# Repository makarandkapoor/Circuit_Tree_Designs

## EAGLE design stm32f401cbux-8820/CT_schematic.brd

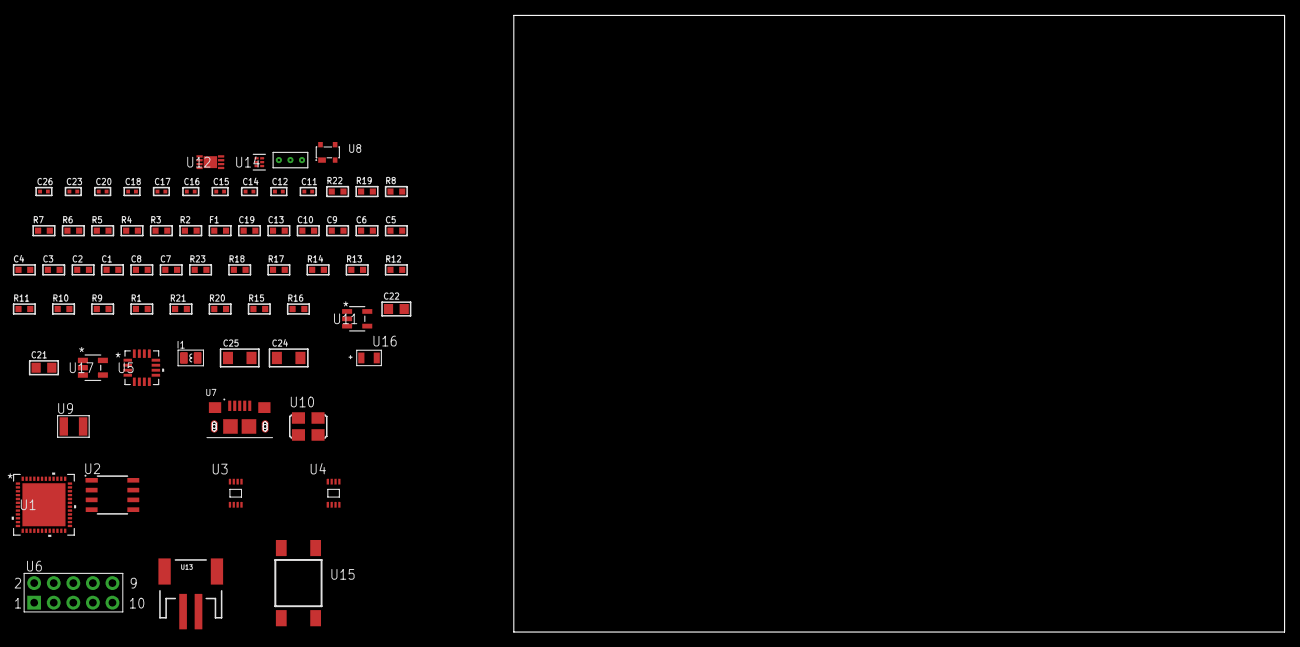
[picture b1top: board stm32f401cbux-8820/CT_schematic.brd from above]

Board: 2 copper layers, 69 parts (0 on the bottom side), 45 nets, no tracks yet.

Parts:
C1, C10, C13, C19: 1e-06; C0603
C2, C3, C4, C5, C6: 1e-07; C0603
C7: 4.7e-06; C0603
C8: 2.2e-06; C0603
C9: 1e-08; C0603
C11, C12: 1e-11; C0402
C14, C15, C16, C20, C26: 1e-08; C0402
C17, C18, C23: 1e-07; C0402
C21, C22: 1e-05; C0805
C24, C25: 1e-05; C1206
F1: 240.0; L0603
I1: 3.3e-06; L0806
R1, R9, R10, R11, R12, R13, R14, R17, R18, R23: 10000.0; R0603
R2: 1000.0; R0603
R3: 1600.5; R0603
R4: 4700.0; R0603
R5, R6, R7, R8: 2200.0; R0603
R15: 220000.0; R0603
R16: 1000000.0; R0603
R19: 9100.0; R0603
R20: 680000.0; R0603
R21: 120000.0; R0603
R22: 2000.0; R0603
U1: stm32f401CBU6; UFQFPN48
U2: AT25040B-SSHL-T; SOIC-8
U3: 24AA04-I/MC; TDFN-8/6MM
U4: 24AA08T-I/MNY; TDFN-8/6MM
U5: TSC2046IRGVR; VQFN-16
U6: HTSS-105-01-G-D
U7: 10118193-0001LF; FCI_10118193-0001LF
U8: prtr5v0u2ax; SOT143B
U9: ABS07-32.768KHZ-7-T
U10: ASFL1-25MHZ-NCS; ASFL1
U11: ltc3406es5; TSOT-23-5
U12: MCP73831T-2ACI/MC; DFN8_2X3MC
U13: S2B-PH-SM4-TB(LF)(SN); JST-2-SMD
U14: TPS3895ADRYR; SON-6
U15: 4-1437565-2; SW_4-1437565-2
U16: Q65110A2395; LGM67K-G1J2-24-Z
U17: nc7sz125m5x; NC7SZ125M5X
U18: Dummy; DUMMY_PACKAGE_149

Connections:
CLK_CRYSTAL_U1_3: C11.1, U1.3, U9.1
CLK_CRYSTAL_U1_4: C12.1, U1.4, U9.2
CLK_U1_5: U1.5, U10.3
GND: C1.2, C2.2, C3.2, C4.2, C5.2, C6.2, C7.2, C8.2, C9.2, C10.2, C11.2, C12.2, C13.2, C14.2, C15.2, C16.2, C17.2, C18.2, C19.2, C20.2, C21.2, C22.1, C22.2, C23.2, C24.2, C25.2, C26.2, R2.2, R9.2, R15.2, R19.2, R21.2, R22.2, U1.8, U1.23, U1.35, U1.47, U1.49, U2.4, U3.4, U4.4, U5.10, U6.9, U7.5, U7.6, U7.7, U7.8, U7.9, U8.1, U10.2, U11.2, U12.6, U12.9, U13.2, U14.2, U16.C, U17.1, U17.3, U18.1
INPUT_USBPOWER_5V: C13.1, C24.1, R23.2, U1.30, U7.1, U8.4, U12.1, U12.2
NET_U1_7: R4.1, U1.7, U17.4
NET_U1_9: C9.1, C10.1, F1.1, U1.9
NET_U1_21: R7.1, U1.21, U3.6
NET_U1_22: C8.1, U1.22
NET_U1_39: R8.1, U1.39, U3.5
NET_U1_42: R5.1, U1.42, U4.6
NET_U1_43: R6.1, U1.43, U4.5
NET_U1_44: R9.1, U1.44
NET_U1_45: R3.1, U1.45, U16.A
NET_U1_46: R1.1, U1.46, U15.3, U15.4
NET_U2_3: R10.1, U2.3
NET_U2_7: R12.1, U2.7
NET_U5_15: R14.1, U5.15
NET_U6_3: U5.7, U6.3
NET_U6_4: U5.9, U6.4
NET_U6_5: U5.6, U6.5
NET_U6_6: U5.8, U6.6
NET_U11_3: I1.1, U11.3
NET_U11_5: R15.1, R16.1, U11.5
NET_U11_ATNET_3: I1.2, R16.2
NET_U12_5: R23.1, U12.5
NET_U12_8: R22.1, U12.8
NET_U14_1: R18.1, R19.1, U14.1
NET_U14_3: R20.2, R21.1, U14.3
NET_U14_4: R17.1, U14.4, U17.2
NET_U15_1: R2.1, U15.1, U15.2
PROC_SPI1_MISO: U1.16, U5.16
PROC_SPI1_MOSI: U1.17, U5.2
PROC_SPI1_NSS: R13.1, U1.14, U5.3
PROC_SPI1_SCK: U1.15, U5.4
PROC_SPI2_MISO: U1.27, U2.2
PROC_SPI2_MOSI: U1.28, U2.5
PROC_SPI2_NSS: R11.1, U1.25, U2.1
PROC_SPI2_SCK: U1.26, U2.6
PROC_TIM1_CH2N: U1.18, U18.2
PROC_TIM1_CH3: U1.31, U18.3
PROC_USB_OTG_FS_DM: U1.32, U7.2, U8.3
PROC_USB_OTG_FS_DP: U1.33, U7.3, U8.2
VCC_S1_3V7: C21.1, C25.1, U11.4, U12.3, U12.4, U13.1
VCC_TIER1_3V3: C1.1, C2.1, C3.1, C4.1, C5.1, C6.1, C7.1, C14.1, C15.1, C16.1, C17.1, C18.1, C19.1, C20.1, C22.2, C23.1, C26.1, F1.2, I1.2, R1.2, R3.2, R4.2, R5.2, R6.2, R7.2, R8.2, R10.2, R11.2, R12.2, R13.2, R14.2, R16.2, R17.2, R18.2, R20.1, U1.1, U1.24, U1.36, U1.48, U2.8, U3.7, U3.8, U4.7, U4.8, U5.5, U5.14, U10.4, U14.6, U17.5

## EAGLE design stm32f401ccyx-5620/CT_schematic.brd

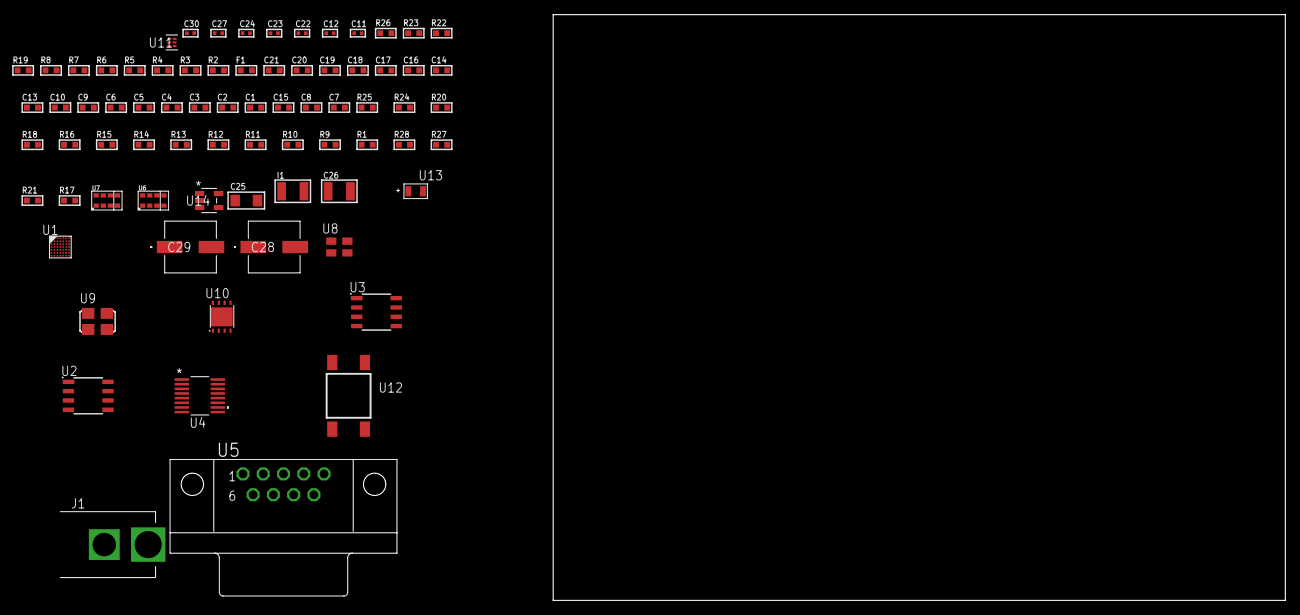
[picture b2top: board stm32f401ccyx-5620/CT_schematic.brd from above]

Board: 2 copper layers, 100.0 x 80.0 mm, 75 parts (0 on the bottom side), 51 nets, no tracks yet.

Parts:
C1, C10, C13, C14, C16, C17, C18, C19, C20, C21: 1e-06; C0603
C2, C3, C4, C5, C6: 1e-07; C0603
C7: 4.7e-06; C0603
C8: 2.2e-06; C0603
C9: 1e-08; C0603
C11, C12, C22, C23, C24, C30: 1e-08; C0402
C15: 2.2e-07; C0603
C25: 1e-05; C1206
C26: 1e-05; C1210
C27: 1e-07; C0402
C28, C29: 0.0001; EXV-9H
F1: 240.0; L0603
I1: 1e-05; L1210
J1: PJ-037B; PJ-037B_PACKAGE
R1, R9, R10, R11, R12, R13, R14, R15, R16, R18, R20, R24, R25: 10000.0; R0603
R2, R23: 1000.0; R0603
R3: 1600.5; R0603
R4: 4700.0; R0603
R5, R6, R7, R8: 2200.0; R0603
R17, R21: 100000.0; R0603
R19: 22.0; R0603
R22: 2231.0; R0603
R26: 9100.0; R0603
R27: 680000.0; R0603
R28: 120000.0; R0603
U1: STM32F401CCY6; WLCSP49
U2: AT25010B-SSHL-T; SOIC-8
U3: AT25640B-SSHL-T; SOIC-8
U4: LTC2804CGN-1#PBF; SSOP-16
U5: 182-009-113R531; 182-009-MALE
U6, U7: TMD27711; SMD-8
U8: ASEK-32.768KHz-ECST; ASEK
U9: ASFL1-25MHZ-NCS; ASFL1
U10: LP3878SDX-ADJ/NOPB; WSON-8
U11: TPS3895ADRYR; SON-6
U12: 4-1437565-2; SW_4-1437565-2
U13: Q65110A2395; LGM67K-G1J2-24-Z
U14: nc7sz125m5x; NC7SZ125M5X

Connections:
CLK_U1_C7: U1.C7, U8.3
CLK_U1_D7: U1.D7, U9.3
GND: C1.2, C2.2, C3.2, C4.2, C5.2, C6.2, C7.2, C8.2, C9.2, C10.2, C11.2, C12.2, C13.2, C14.2, C16.2, C17.2, C18.2, C19.2, C20.2, C21.2, C22.2, C23.2, C24.2, C25.2, C26.2, C27.2, C28.2, C29.2, C30.2, J1.2, R2.2, R9.2, R23.2, R26.2, R28.2, U1.A6, U1.B1, U1.D3, U1.E6, U2.4, U3.4, U4.8, U5.5, U6.3, U7.3, U8.2, U9.2, U10.3, U10.PAD, U11.2, U13.C, U14.1, U14.3
NET_U1_A3: R8.1, U1.A3, U7.8
NET_U1_A5: R9.1, U1.A5
NET_U1_B5: R5.1, U1.B5, U6.2
NET_U1_B6: R10.1, U1.B6
NET_U1_C5: R6.1, U1.C5, U6.8
NET_U1_E3: R7.1, U1.E3, U7.2
NET_U1_E7: R4.1, U1.E7, U14.4
NET_U1_F7: C9.1, C10.1, F1.1, U1.F7
NET_U1_G2: C8.1, U1.G2
NET_U1_G6: R3.1, U1.G6, U13.A
NET_U1_G7: R1.1, U1.G7, U12.3, U12.4
NET_U2_3: R11.1, U2.3
NET_U2_7: R13.1, U2.7
NET_U3_3: R14.1, U3.3
NET_U3_7: R16.1, U3.7
NET_U4_6: C13.1, U4.6
NET_U4_7: C15.1, I1.2, U4.7
NET_U4_9: C14.1, U4.9
NET_U4_10: C15.2, U4.10
NET_U4_11: R17.1, U4.11
NET_U5_2: U4.1, U5.2
NET_U5_3: U4.3, U5.3
NET_U5_7: U4.2, U5.7
NET_U5_8: U4.4, U5.8
NET_U6_4: C19.1, R19.1, U6.4
NET_U6_7: R18.1, U6.7
NET_U7_7: R20.1, U7.7
NET_U10_1: C24.1, U10.1
NET_U10_6: R22.2, R23.1, U10.6
NET_U10_8: R21.1, U10.8
NET_U11_1: R25.1, R26.1, U11.1
NET_U11_3: R27.2, R28.1, U11.3
NET_U11_4: R24.1, U11.4, U14.2
NET_U12_1: R2.1, U12.1, U12.2
PROC_SPI1_MISO: U1.A4, U2.2
PROC_SPI1_MOSI: U1.B4, U2.5
PROC_SPI1_NSS: R12.1, U1.A2, U2.1
PROC_SPI1_SCK: U1.F5, U2.6
PROC_SPI2_MISO: U1.F1, U3.2
PROC_SPI2_MOSI: U1.E1, U3.5
PROC_SPI2_NSS: R15.1, U1.E2, U3.1
PROC_SPI2_SCK: U1.G1, U3.6
PROC_USART1_CTS: U1.C1, U4.13
PROC_USART1_RTS: U1.C3, U4.15
PROC_USART1_RX: U1.C2, U4.16
PROC_USART1_TX: U1.C4, U4.14
VCC_S1_5V3: C25.1, C28.1, C29.1, J1.1, R21.2, U10.4
VCC_TIER1_3V3: C1.1, C2.1, C3.1, C4.1, C5.1, C6.1, C7.1, C11.1, C12.1, C16.1, C17.1, C18.1, C20.1, C21.1, C22.1, C23.1, C26.1, C27.1, C30.1, F1.2, I1.1, R1.2, R3.2, R4.2, R5.2, R6.2, R7.2, R8.2, R10.2, R11.2, R12.2, R13.2, R14.2, R15.2, R16.2, R17.2, R18.2, R19.2, R20.2, R22.1, R24.2, R25.2, R27.1, U1.A7, U1.B2, U1.B7, U1.F2, U2.8, U3.8, U4.5, U4.12, U6.1, U7.1, U7.4, U8.4, U9.4, U10.5, U11.6, U14.5

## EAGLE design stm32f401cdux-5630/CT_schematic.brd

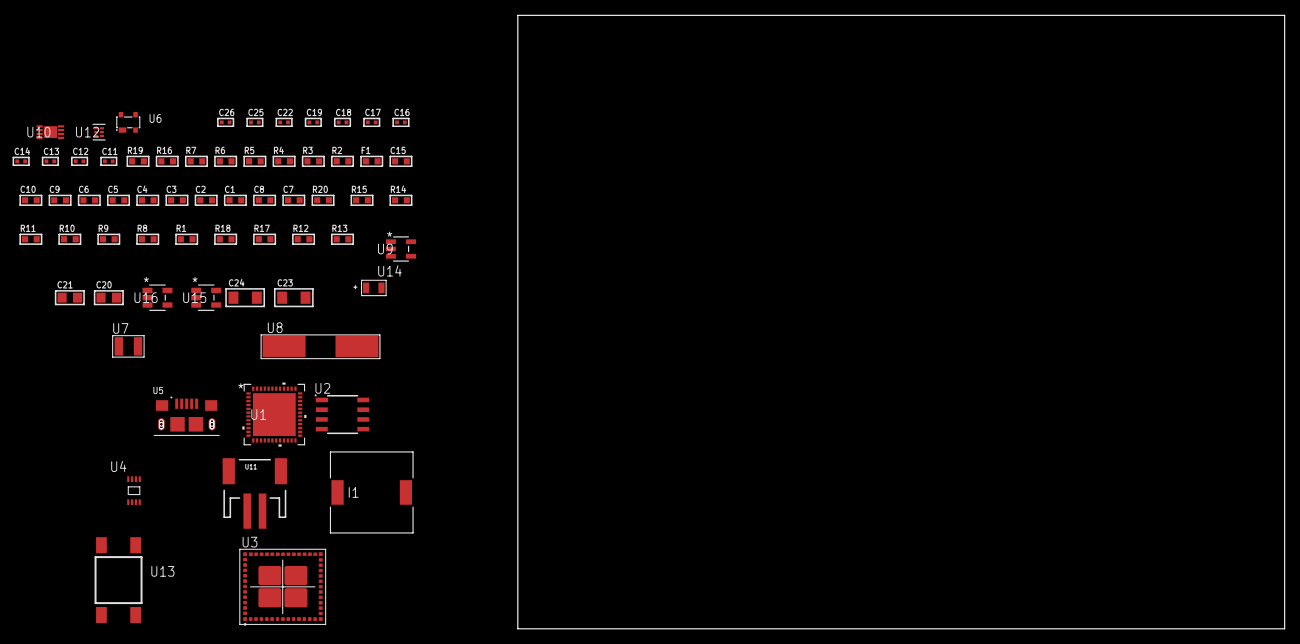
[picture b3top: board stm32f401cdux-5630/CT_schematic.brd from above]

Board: 2 copper layers, 64 parts (0 on the bottom side), 38 nets, no tracks yet.

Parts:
C1, C10, C15: 1e-06; C0603
C2, C3, C4, C5, C6: 1e-07; C0603
C7: 4.7e-06; C0603
C8: 2.2e-06; C0603
C9: 1e-08; C0603
C11, C12, C13, C14: 1e-11; C0402
C16, C19, C25, C26: 1e-08; C0402
C17, C18, C22: 1e-07; C0402
C20, C21: 1e-05; C0805
C23, C24: 1e-05; C1206
F1: 240.0; L0603
I1: 5.2e-06; DR1040
R1, R8, R9, R10, R11, R14, R15, R20: 10000.0; R0603
R2: 1000.0; R0603
R3: 1600.5; R0603
R4, R5: 4700.0; R0603
R6, R7: 2200.0; R0603
R12: 220000.0; R0603
R13: 1000000.0; R0603
R16: 9100.0; R0603
R17: 680000.0; R0603
R18: 120000.0; R0603
R19: 2000.0; R0603
U1: STM32F401CDU6; UFQFPN48
U2: AT25512N-SH-T; SOIC-8
U3: MBH7BLZ02-109004
U4: 24AA00T-I/MNY; TDFN-8/6MM
U5: 10118193-0001LF; FCI_10118193-0001LF
U6: prtr5v0u2ax; SOT143B
U7: ABS07-32.768KHZ-7-T
U8: ABLS-25.000MHZ-B2F-T
U9: ltc3406es5; TSOT-23-5
U10: MCP73831T-2ACI/MC; DFN8_2X3MC
U11: S2B-PH-SM4-TB(LF)(SN); JST-2-SMD
U12: TPS3895ADRYR; SON-6
U13: 4-1437565-2; SW_4-1437565-2
U14: Q65110A2395; LGM67K-G1J2-24-Z
U15, U16: nc7sz125m5x; NC7SZ125M5X

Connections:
CLK_CRYSTAL_U1_3: C11.1, U1.3, U7.1
CLK_CRYSTAL_U1_4: C12.1, U1.4, U7.2
CLK_CRYSTAL_U1_5: C13.1, U1.5, U8.1
CLK_CRYSTAL_U1_6: C14.1, U1.6, U8.2
GND: C1.2, C2.2, C3.2, C4.2, C5.2, C6.2, C7.2, C8.2, C9.2, C10.2, C11.2, C12.2, C13.2, C14.2, C15.2, C16.2, C17.2, C18.2, C19.2, C20.2, C21.1, C21.2, C22.2, C23.2, C24.2, C25.2, C26.2, R2.2, R8.2, R12.2, R16.2, R18.2, R19.2, U1.8, U1.23, U1.35, U1.47, U1.49, U2.4, U3.1, U3.3, U3.15, U3.27, U3.29, U3.41, U3.42, U3.43, U3.44, U3.45, U3.46, U3.47, U3.48, U3.49, U3.50, U3.52, U3.53, U3.54, U3.55, U3.56, U4.4, U5.5, U5.6, U5.7, U5.8, U5.9, U6.1, U9.2, U10.6, U10.9, U11.2, U12.2, U14.C, U15.1, U15.3, U16.1, U16.3
INPUT_USBPOWER_5V: C15.1, C23.1, R20.2, U1.30, U5.1, U6.4, U10.1, U10.2
NET_U1_7: R5.1, U1.7, U16.4
NET_U1_9: C9.1, C10.1, F1.1, U1.9
NET_U1_22: C8.1, U1.22
NET_U1_42: R6.1, U1.42, U4.6
NET_U1_43: R7.1, U1.43, U4.5
NET_U1_44: R8.1, U1.44
NET_U1_45: R3.1, U1.45, U14.A
NET_U1_46: R1.1, U1.46, U13.3, U13.4
NET_U2_3: R9.1, U2.3
NET_U2_7: R11.1, U2.7
NET_U3_39: R4.1, U3.39, U15.4
NET_U9_3: I1.1, U9.3
NET_U9_5: R12.1, R13.1, U9.5
NET_U9_ATNET_3: I1.2, R13.2
NET_U10_5: R20.1, U10.5
NET_U10_8: R19.1, U10.8
NET_U12_1: R15.1, R16.1, U12.1
NET_U12_3: R17.2, R18.1, U12.3
NET_U12_4: R14.1, U12.4, U15.2, U16.2
NET_U13_1: R2.1, U13.1, U13.2
PROC_SPI1_MISO: U1.16, U2.2
PROC_SPI1_MOSI: U1.17, U2.5
PROC_SPI1_NSS: R10.1, U1.14, U2.1
PROC_SPI1_SCK: U1.15, U2.6
PROC_USART2_CTS: U1.10, U3.26
PROC_USART2_RTS: U1.11, U3.24
PROC_USART2_RX: U1.13, U3.25
PROC_USART2_TX: U1.12, U3.23
PROC_USB_OTG_FS_DM: U1.32, U5.2, U6.3
PROC_USB_OTG_FS_DP: U1.33, U5.3, U6.2
VCC_S1_3V7: C20.1, C24.1, U9.4, U10.3, U10.4, U11.1
VCC_TIER1_3V3: C1.1, C2.1, C3.1, C4.1, C5.1, C6.1, C7.1, C16.1, C17.1, C18.1, C19.1, C21.2, C22.1, C25.1, C26.1, F1.2, I1.2, R1.2, R3.2, R4.2, R5.2, R6.2, R7.2, R9.2, R10.2, R11.2, R13.2, R14.2, R15.2, R17.1, U1.1, U1.24, U1.36, U1.48, U2.8, U3.28, U4.8, U12.6, U15.5, U16.5

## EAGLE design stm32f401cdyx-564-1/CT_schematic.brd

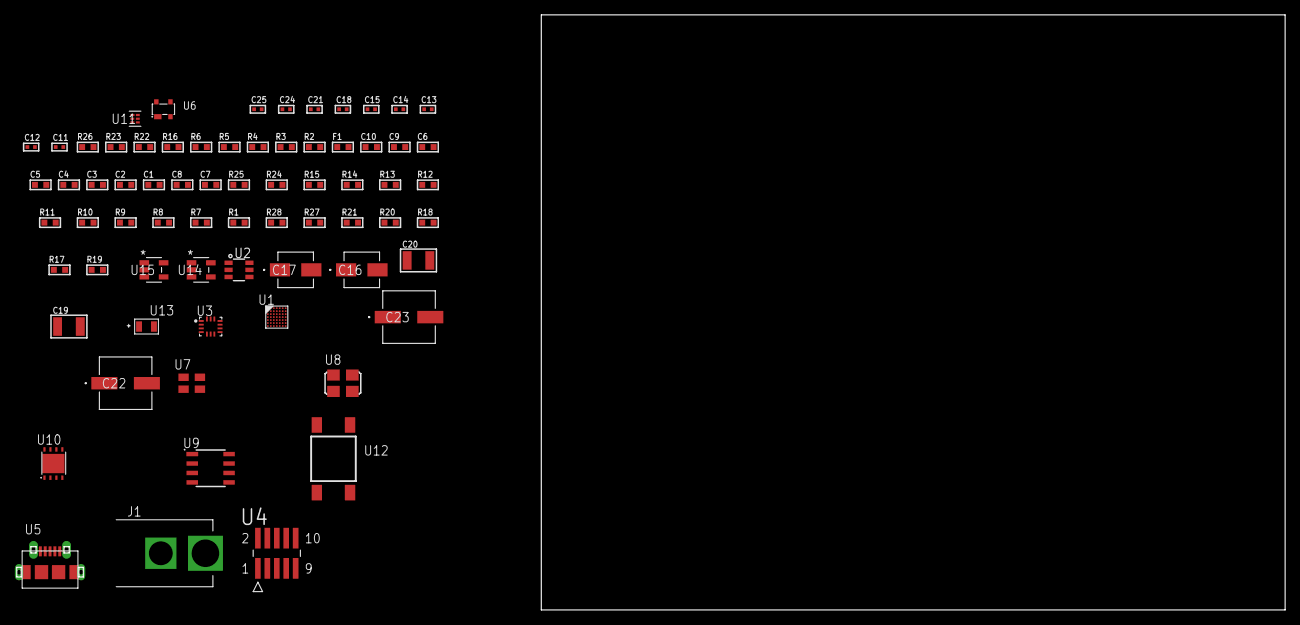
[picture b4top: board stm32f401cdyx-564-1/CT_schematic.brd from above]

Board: 2 copper layers, 170.5 x 80.0 mm, 70 parts (0 on the bottom side), 39 nets, no tracks yet.

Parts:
C1, C10: 1e-06; C0603
C2, C3, C4, C5, C6: 1e-07; C0603
C7: 4.7e-06; C0603
C8: 2.2e-06; C0603
C9: 1e-08; C0603
C11, C12, C13, C21: 1e-07; C0402
C14, C15, C18, C24, C25: 1e-08; C0402
C16: 1e-06; EXV-9B
C17: 2.2e-06; EXV-9B
C19, C20: 1e-05; C1210
C22, C23: 0.0001; EXV-9H
F1: 240.0; L0603
J1: PJ-037B; PJ-037B_PACKAGE
R1, R8, R9, R10, R11, R12, R13, R14, R15, R24, R25: 10000.0; R0603
R2, R23: 1000.0; R0603
R3: 1600.5; R0603
R4: 4700.0; R0603
R5, R6: 2200.0; R0603
R7: 47000.0; R0603
R16: 5.0; R0603
R17, R18, R20, R21: 100000.0; R0603
R19: 164658.62; R0603
R22: 3900.0; R0603
R26: 9100.0; R0603
R27: 680000.0; R0603
R28: 120000.0; R0603
U1: STM32F401CDY6; WLCSP49
U2: MAX4995AAUT+T; SOT-23-6
U3: BMG250; LGA-14
U4: FTSH-105-01-L-DV-K; SAMTEC_FTSH-105-01-L-DV-K
U5: 47590-0001; MICRO_USB_AB
U6: prtr5v0u2ax; SOT143B
U7: ASEK-32.768KHz-ECST; ASEK
U8: ASFL1-25MHZ-NCS; ASFL1
U9: LP2954AIMX/NOPB; LP2954
U10: LP3878SDX-ADJ/NOPB; WSON-8
U11: TPS3895ADRYR; SON-6
U12: 4-1437565-2; SW_4-1437565-2
U13: Q65110A2395; LGM67K-G1J2-24-Z
U14, U15: nc7sz125m5x; NC7SZ125M5X

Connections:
CLK_U1_C7: U1.C7, U7.3
CLK_U1_D7: U1.D7, U8.3
GND: C1.2, C2.2, C3.2, C4.2, C5.2, C6.2, C7.2, C8.2, C9.2, C10.2, C11.2, C12.2, C13.2, C14.2, C15.2, C16.2, C17.2, C18.2, C19.2, C20.2, C21.2, C22.2, C23.2, C24.2, C25.2, J1.2, R2.2, R7.2, R8.2, R11.2, R16.2, R20.2, R23.2, R26.2, R28.2, U1.A6, U1.B1, U1.D3, U1.E6, U2.2, U3.1, U3.6, U3.7, U4.3, U4.5, U5.5, U5.6, U5.7, U5.8, U5.9, U6.1, U7.2, U8.2, U9.4, U10.3, U10.PAD, U11.2, U13.C, U14.2, U14.3, U15.1, U15.3
NET_U1_A5: R8.1, U1.A5
NET_U1_B5: R5.1, U1.B5, U3.13
NET_U1_B6: R9.1, U1.B6
NET_U1_C5: R6.1, U1.C5, U3.14
NET_U1_E7: R4.1, U1.E7, U15.4
NET_U1_F7: C9.1, C10.1, F1.1, U1.F7
NET_U1_G2: C8.1, U1.G2
NET_U1_G6: R3.1, U1.G6, U13.A
NET_U1_G7: R1.1, U1.G7, U12.3, U12.4
NET_U2_3: R7.1, U2.3
NET_U3_12: R12.1, U3.12
NET_U4_9: R16.1, U4.9
NET_U9_3: R18.1, U9.3
NET_U9_5: R17.1, U9.5
NET_U9_7: R19.2, R20.1, U9.7
NET_U10_1: C18.1, U10.1
NET_U10_6: R22.2, R23.1, U10.6
NET_U10_8: R21.1, U10.8
NET_U11_1: R25.1, R26.1, U11.1
NET_U11_3: R27.2, R28.1, U11.3
NET_U11_4: R24.1, U11.4, U14.4, U15.2
NET_U12_1: R2.1, U12.1, U12.2
PROC_GPIO_TO_U1_USB_FAULT: R10.1, U1.A4, U2.6
PROC_GPIO_TO_U1_VBUS_EN: R11.1, U1.A2, U2.4
PROC_GPIO_TO_U3_INT1: U1.B4, U3.4
PROC_SYS_JTCK_SWCLK: R14.1, U1.A1, U4.4
PROC_SYS_JTDO_SWO: U1.A3, U4.6
PROC_SYS_JTMS_SWDIO: R15.1, U1.B3, U4.2
PROC_USB_OTG_FS_DM: U1.C1, U5.2, U6.3
PROC_USB_OTG_FS_DP: U1.C3, U5.3, U6.2
PROC_USB_OTG_FS_ID: U1.C2, U5.4
PROC_USB_OTG_FS_VBUS: U1.D2, U2.1, U5.1, U6.4
RST_OUT_U4_JTAG_RST_B: R13.1, U4.10, U14.1
VCC_S1_12V5: C16.1, C19.1, C22.1, C23.1, J1.1, R18.2, R21.2, U9.8, U10.4
VCC_TIER1_3V3: C1.1, C2.1, C3.1, C4.1, C5.1, C6.1, C7.1, C11.1, C12.1, C13.1, C14.1, C15.1, C17.1, C21.1, C24.1, C25.1, F1.2, R1.2, R3.2, R4.2, R5.2, R6.2, R9.2, R10.2, R12.2, R13.2, R14.2, R15.2, R17.2, R19.1, R24.2, R25.2, R27.1, U1.A7, U1.B2, U1.B7, U1.F2, U3.5, U3.8, U4.1, U7.4, U8.4, U9.1, U11.6, U14.5, U15.5
VCC_TIER1_5V0: C20.1, R22.1, U2.5, U10.5

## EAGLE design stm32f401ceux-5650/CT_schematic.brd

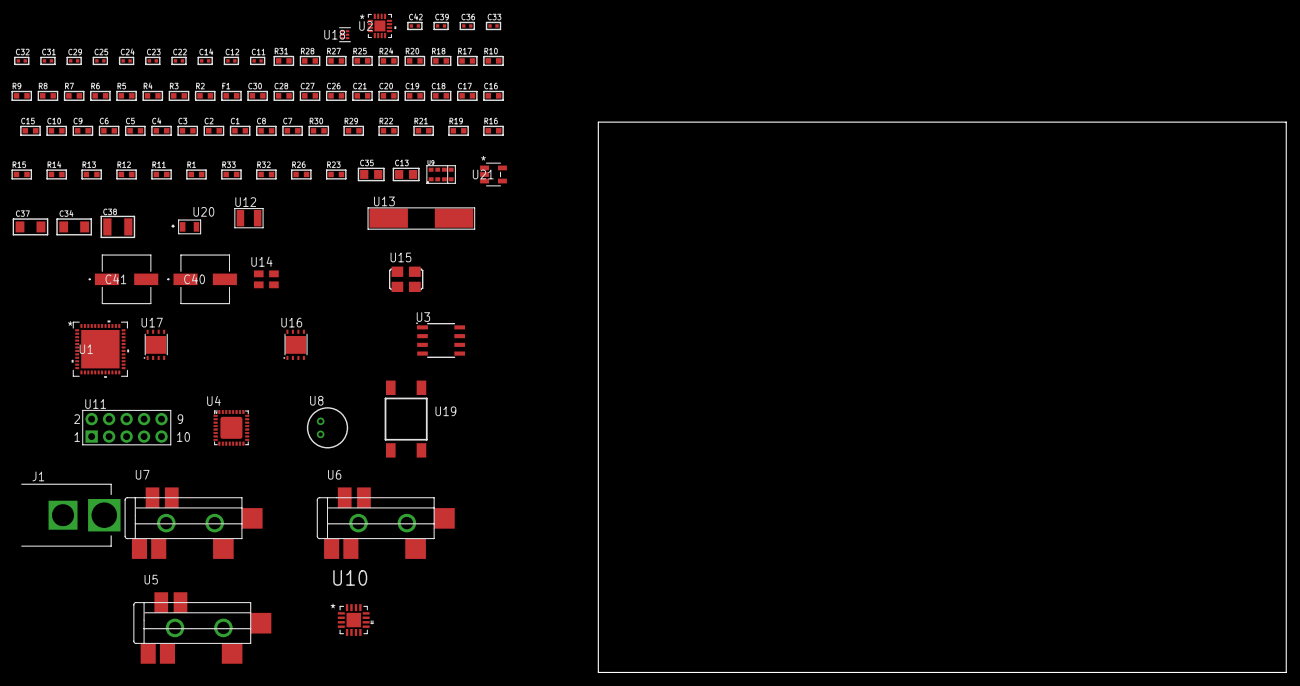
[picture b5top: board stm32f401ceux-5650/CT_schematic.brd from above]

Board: 2 copper layers, 100.0 x 80.0 mm, 98 parts (0 on the bottom side), 65 nets, no tracks yet.

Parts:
C1, C10, C15, C16, C17, C18, C19, C20, C21, C26, C27, C28, C30: 1e-06; C0603
C2, C3, C4, C5, C6: 1e-07; C0603
C7: 4.7e-06; C0603
C8: 2.2e-06; C0603
C9: 1e-08; C0603
C11, C12: 1e-11; C0402
C13: 4.7e-06; C0805
C14, C31, C32, C33, C36, C42: 1e-08; C0402
C22, C23, C24, C25, C29, C39: 1e-07; C0402
C34, C37: 1e-05; C1206
C35: 1e-05; C0805
C38: 1e-05; C1210
C40, C41: 0.0001; EXV-9H
F1: 240.0; L0603
J1: PJ-037B; PJ-037B_PACKAGE
R1, R11, R12, R13, R14, R15, R16, R19, R21, R22, R29, R30: 10000.0; R0603
R2, R25, R28: 1000.0; R0603
R3: 1600.5; R0603
R4: 4700.0; R0603
R5, R6, R7, R8, R9, R10: 2200.0; R0603
R17, R18: 1270.0; R0603
R20: 22.0; R0603
R23, R26: 100000.0; R0603
R24: 200.0; R0603
R27: 2231.0; R0603
R31: 9100.0; R0603
R32: 680000.0; R0603
R33: 120000.0; R0603
U1: STM32F401CEU6; UFQFPN48
U2: M41T65Q6F; M41T65_QFN-16
U3: 24AA1025T-I/SN; SOIC-8
U4: SGTL5000XNAA3; QFN-32
U5, U6, U7: SJ-43515TS-SMT-TR
U8: WM-64PCT; WM-64PC
U9: TMD27711; SMD-8
U10: TSC2008TRGVRQ1; QFN65P400X400X100-17N
U11: HTSS-105-01-G-D
U12: ABS07-32.768KHZ-7-T
U13: ABLS-25.000MHZ-B2F-T
U14: ASEK-32.768KHz-ECST; ASEK
U15: ASFL-24.57MHZ-NCS; ASFL1
U16, U17: LP3878SDX-ADJ/NOPB; WSON-8
U18: TPS3895ADRYR; SON-6
U19: 4-1437565-2; SW_4-1437565-2
U20: Q65110A2395; LGM67K-G1J2-24-Z
U21: nc7sz125m5x; NC7SZ125M5X

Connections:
CLK_CRYSTAL_U1_5: C11.1, U1.5, U13.1
CLK_CRYSTAL_U1_6: C12.1, U1.6, U13.2
CLK_CRYSTAL_U2_1: U2.1, U12.1
CLK_CRYSTAL_U2_2: U2.2, U12.2
CLK_U1_3: U1.3, U14.3
CLK_U4_21: U4.21, U15.3
GND: C1.2, C2.2, C3.2, C4.2, C5.2, C6.2, C7.2, C8.2, C9.2, C10.2, C11.2, C12.2, C13.2, C14.2, C22.2, C23.2, C24.2, C25.2, C26.2, C27.2, C28.2, C29.2, C30.2, C31.2, C32.2, C33.2, C34.2, C35.2, C36.2, C37.2, C38.2, C39.2, C40.2, C41.2, C42.2, J1.2, R2.2, R11.2, R18.2, R25.2, R28.2, R31.2, R33.2, U1.8, U1.23, U1.35, U1.47, U1.49, U2.3, U2.5, U2.17, U3.4, U3.7, U4.1, U4.3, U4.7, U4.EXP, U6.1, U7.1, U8.2, U9.3, U10.10, U10.12, U10.17, U11.9, U14.2, U15.2, U16.3, U16.PAD, U17.3, U17.PAD, U18.2, U20.C, U21.1, U21.3
NET_U1_7: R4.1, U1.7, U21.4
NET_U1_9: C9.1, C10.1, F1.1, U1.9
NET_U1_21: R7.1, U1.21, U2.10
NET_U1_22: C8.1, U1.22
NET_U1_29: R9.1, U1.29, U3.6
NET_U1_39: R8.1, U1.39, U2.9
NET_U1_40: R10.1, U1.40, U3.5
NET_U1_42: R5.1, U1.42, U9.2
NET_U1_43: R6.1, U1.43, U9.8
NET_U1_44: R11.1, U1.44
NET_U1_45: R3.1, U1.45, U20.A
NET_U1_46: R1.1, U1.46, U19.3, U19.4
NET_U2_4: R12.1, U2.4
NET_U2_11: R13.1, U2.11
NET_U3_1: R15.1, U3.1
NET_U3_2: R16.1, U3.2
NET_U3_3: R14.1, U3.3
NET_U4_10: C25.1, U4.10
NET_U4_29: R17.1, U4.29
NET_U4_31: R18.1, U4.31
NET_U5_1: U4.4, U5.1
NET_U5_2: U4.2, U5.2
NET_U5_5: U4.6, U5.5
NET_U6_2: C16.1, U6.2
NET_U6_5: C15.1, U6.5
NET_U7_2: C18.1, C19.1, U7.2
NET_U7_5: C17.1, U7.5
NET_U7_13: C18.2, C19.2
NET_U8_1: C20.1, C21.1, C26.1, U4.16, U8.1
NET_U8_15: C20.2, C21.2
NET_U9_4: C28.1, R20.1, U9.4
NET_U9_7: R19.1, U9.7
NET_U10_15: R22.1, U10.15
NET_U11_3: U10.7, U11.3
NET_U11_4: U10.9, U11.4
NET_U11_5: U10.6, U11.5
NET_U11_6: U10.8, U11.6
NET_U16_1: C33.1, U16.1
NET_U16_6: R24.2, R25.1, U16.6
NET_U16_8: R23.1, U16.8
NET_U17_1: C36.1, U17.1
NET_U17_6: R27.2, R28.1, U17.6
NET_U17_8: R26.1, U17.8
NET_U18_1: R30.1, R31.1, U18.1
NET_U18_3: R32.2, R33.1, U18.3
NET_U18_4: R29.1, U18.4, U21.2
NET_U19_1: R2.1, U19.1, U19.2
PROC_I2S2_CK: U1.26, U4.24
PROC_I2S2_EXT_SD: U1.27, U4.25
PROC_I2S2_SD: U1.28, U4.26
PROC_I2S2_WS: U1.25, U4.23
PROC_SPI1_MISO: U1.16, U10.16
PROC_SPI1_MOSI: U1.17, U10.2
PROC_SPI1_NSS: R21.1, U1.14, U10.3
PROC_SPI1_SCK: U1.15, U10.4
VCC_S1_5V9: C34.1, C37.1, C40.1, C41.1, J1.1, R23.2, R26.2, U16.4, U17.4
VCC_TIER1_1V2: C22.1, C35.1, R24.1, U4.30, U16.5
VCC_TIER1_3V3: C1.1, C2.1, C3.1, C4.1, C5.1, C6.1, C7.1, C13.1, C14.1, C23.1, C24.1, C27.1, C29.1, C30.1, C31.1, C32.1, C38.1, C39.1, C42.1, F1.2, R1.2, R3.2, R4.2, R5.2, R6.2, R7.2, R8.2, R9.2, R10.2, R12.2, R13.2, R14.2, R15.2, R16.2, R17.2, R19.2, R20.2, R21.2, R22.2, R27.1, R29.2, R30.2, R32.1, U1.1, U1.24, U1.36, U1.48, U2.14, U3.8, U4.5, U4.20, U9.1, U10.5, U14.4, U15.4, U17.5, U18.6, U21.5

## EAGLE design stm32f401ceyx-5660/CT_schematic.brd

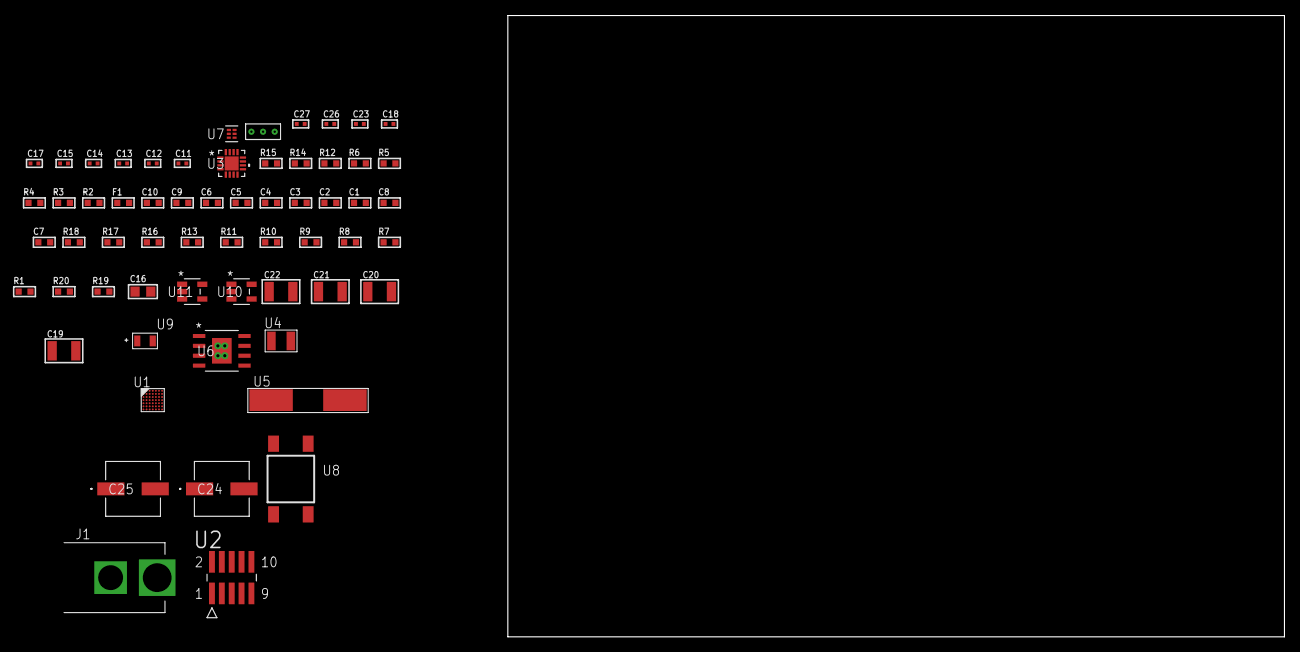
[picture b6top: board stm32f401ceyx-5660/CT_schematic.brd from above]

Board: 2 copper layers, 100.0 x 80.0 mm, 61 parts (0 on the bottom side), 30 nets, no tracks yet.

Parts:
C1, C10: 1e-06; C0603
C2, C3, C4, C5, C6: 1e-07; C0603
C7: 4.7e-06; C0603
C8: 2.2e-06; C0603
C9: 1e-08; C0603
C11, C12, C13, C14: 1e-11; C0402
C15, C17, C18, C23: 1e-07; C0402
C16: 4.7e-06; C0805
C19, C20, C21, C22: 1e-05; C1210
C24, C25: 0.0001; EXV-9H
C26, C27: 1e-08; C0402
F1: 240.0; L0603
J1: PJ-037B; PJ-037B_PACKAGE
R1, R7, R8, R9, R10, R11, R13, R16, R17: 10000.0; R0603
R2: 1000.0; R0603
R3: 1270.0; R0603
R4: 4700.0; R0603
R5, R6, R15: 2200.0; R0603
R12: 5.0; R0603
R14: 2700.0; R0603
R18: 18000.0; R0603
R19: 470000.0; R0603
R20: 120000.0; R0603
U1: STM32F401CEY6; WLCSP49
U2: FTSH-105-01-L-DV-K; SAMTEC_FTSH-105-01-L-DV-K
U3: MMA8451QT; QFN-16
U4: ABS07-32.768KHZ-7-T
U5: ABLS-25.000MHZ-B2F-T
U6: MIC5234YME; SOIC-8_EP
U7: TPS3895ADRYR; SON-6
U8: 4-1437565-2; SW_4-1437565-2
U9: Q65110A2395; LGM67K-G1J2-24-Z
U10, U11: nc7sz125m5x; NC7SZ125M5X
U12: Dummy; DUMMY_PACKAGE_122

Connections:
CLK_CRYSTAL_U1_C6: C11.1, U1.C6, U4.1
CLK_CRYSTAL_U1_C7: C12.1, U1.C7, U4.2
CLK_CRYSTAL_U1_D6: C13.1, U1.D6, U5.1
CLK_CRYSTAL_U1_D7: C14.1, U1.D7, U5.2
GND: C1.2, C2.2, C3.2, C4.2, C5.2, C6.2, C7.2, C8.2, C9.2, C10.2, C11.2, C12.2, C13.2, C14.2, C15.2, C16.2, C17.2, C18.2, C19.2, C20.2, C21.2, C22.2, C23.2, C24.2, C25.2, C26.2, C27.2, J1.2, R2.2, R7.2, R12.2, R13.2, R15.2, R18.2, R20.2, U1.A6, U1.B1, U1.D3, U1.E6, U2.3, U2.5, U3.5, U3.10, U3.12, U3.17, U6.7, U6.EPAD, U7.2, U9.C, U10.2, U10.3, U11.1, U11.3, U12.1
NET_U1_A5: R7.1, U1.A5
NET_U1_B5: R5.1, U1.B5, U3.4
NET_U1_B6: R8.1, U1.B6
NET_U1_C5: R6.1, U1.C5, U3.6
NET_U1_E7: R4.1, U1.E7, U11.4
NET_U1_F7: C9.1, C10.1, F1.1, U1.F7
NET_U1_G2: C8.1, U1.G2
NET_U1_G6: R3.1, U1.G6, U9.A
NET_U1_G7: R1.1, U1.G7, U8.3, U8.4
NET_U2_9: R12.1, U2.9
NET_U3_2: C18.1, U3.2
NET_U3_7: R13.1, U3.7
NET_U6_4: R14.2, R15.1, U6.4
NET_U7_1: R17.1, R18.1, U7.1
NET_U7_3: R19.2, R20.1, U7.3
NET_U7_4: R16.1, U7.4, U10.4, U11.2
NET_U8_1: R2.1, U8.1, U8.2
PROC_ADC1_IN2: U1.E5, U12.2
PROC_ADC1_IN3: U1.E4, U12.3
PROC_SYS_JTCK_SWCLK: R10.1, U1.A1, U2.4
PROC_SYS_JTDO_SWO: U1.A3, U2.6
PROC_SYS_JTMS_SWDIO: R11.1, U1.B3, U2.2
RST_OUT_U2_JTAG_RST_B: R9.1, U2.10, U10.1
VCC_S1_6V0: C19.1, C20.1, C24.1, C25.1, J1.1, U6.5, U6.8
VCC_TIER1_2V5: C1.1, C2.1, C3.1, C4.1, C5.1, C6.1, C7.1, C15.1, C16.1, C17.1, C21.1, C22.1, C23.1, C26.1, C27.1, F1.2, R1.2, R3.2, R4.2, R5.2, R6.2, R8.2, R9.2, R10.2, R11.2, R14.1, R16.2, R17.2, R19.1, U1.A7, U1.B2, U1.B7, U1.F2, U2.1, U3.1, U3.14, U6.1, U7.6, U10.5, U11.5

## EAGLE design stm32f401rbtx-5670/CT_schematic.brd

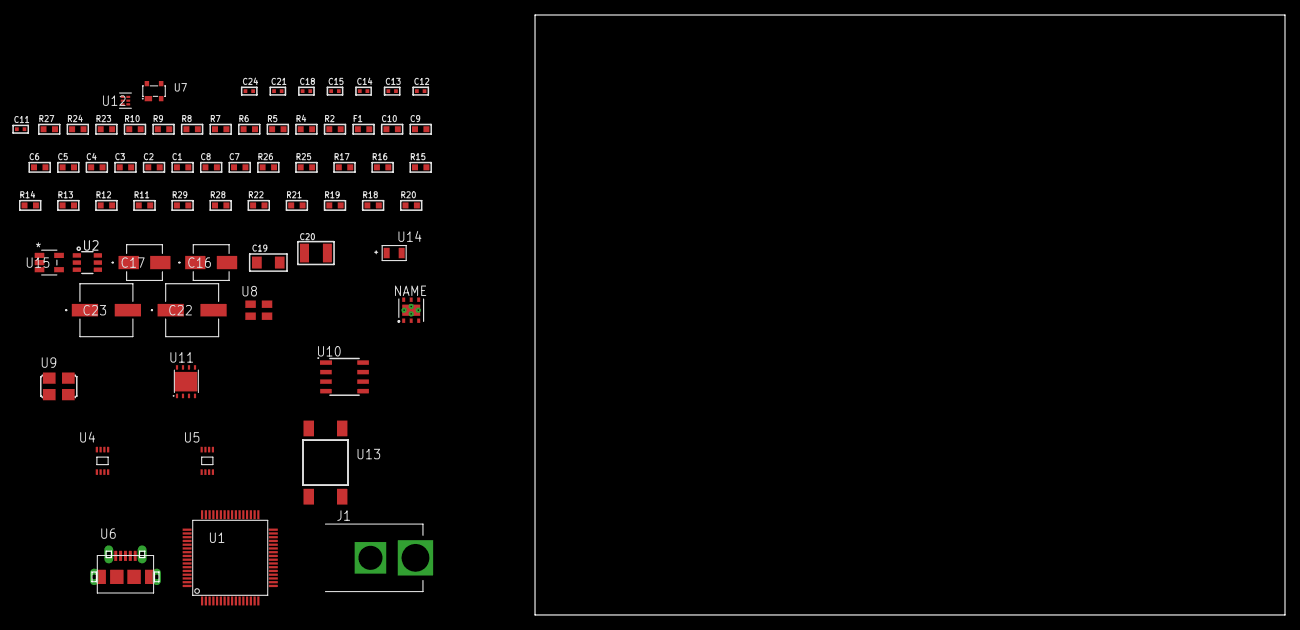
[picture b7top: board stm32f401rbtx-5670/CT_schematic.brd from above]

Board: 2 copper layers, 159.1 x 80.0 mm, 68 parts (0 on the bottom side), 37 nets, no tracks yet.

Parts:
C1, C10: 1e-06; C0603
C2, C3, C4, C5, C6: 1e-07; C0603
C7: 4.7e-06; C0603
C8: 2.2e-06; C0603
C9: 1e-08; C0603
C11, C12, C13, C14, C15, C18, C24: 1e-08; C0402
C16: 1e-06; EXV-9B
C17: 2.2e-06; EXV-9B
C19: 1e-05; C1206
C20: 1e-05; C1210
C21: 1e-07; C0402
C22, C23: 0.0001; EXV-9H
F1: 240.0; L0603
J1: PJ-037B; PJ-037B_PACKAGE
R2, R24: 1000.0; R0603
R4: 4700.0; R0603
R5, R6, R7, R8, R9, R10: 2200.0; R0603
R11: 47000.0; R0603
R12, R13, R14, R15, R16, R17, R25, R26: 10000.0; R0603
R18, R19, R21, R22: 100000.0; R0603
R20: 164658.62; R0603
R23: 3900.0; R0603
R27: 9100.0; R0603
R28: 680000.0; R0603
R29: 120000.0; R0603
U1: STM32F401RBT6; LQFP64
U2: MAX4995AAUT+T; SOT-23-6
U3: HDC1080DMBR; WSON-6
U4: 24AA00T-I/MNY; TDFN-8/6MM
U5: 24AA128T-I/MNY; TDFN-8/6MM
U6: 47590-0001; MICRO_USB_AB
U7: prtr5v0u2ax; SOT143B
U8: ASEK-32.768KHz-ECST; ASEK
U9: ASFL1-25MHZ-NCS; ASFL1
U10: LP2954AIMX/NOPB; LP2954
U11: LP3878SDX-ADJ/NOPB; WSON-8
U12: TPS3895ADRYR; SON-6
U13: 4-1437565-2; SW_4-1437565-2
U14: Q65110A2395; LGM67K-G1J2-24-Z
U15: nc7sz125m5x; NC7SZ125M5X

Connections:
CLK_U1_3: U1.3, U8.3
CLK_U1_5: U1.5, U9.3
GND: C1.2, C2.2, C3.2, C4.2, C5.2, C6.2, C7.2, C8.2, C9.2, C10.2, C11.2, C12.2, C13.2, C14.2, C15.2, C16.2, C17.2, C18.2, C19.2, C20.2, C21.2, C22.2, C23.2, C24.2, J1.2, R2.2, R11.2, R12.2, R14.2, R21.2, R24.2, R27.2, R29.2, U1.12, U1.18, U1.31, U1.47, U1.63, U2.2, U3.2, U3.PAD, U4.4, U5.4, U5.7, U6.5, U6.6, U6.7, U6.8, U6.9, U7.1, U8.2, U9.2, U10.4, U11.3, U11.PAD, U12.2, U14.C, U15.1, U15.3
NET_U1_7: R4.1, U1.7, U15.4
NET_U1_13: C9.1, C10.1, F1.1, U1.13
NET_U1_29: R7.1, U1.29, U4.6
NET_U1_30: C8.1, U1.30
NET_U1_40: R10.1, U1.40, U5.5
NET_U1_41: R9.1, U1.41, U5.6
NET_U1_55: R8.1, U1.55, U4.5
NET_U1_58: R5.1, U1.58, U3.6
NET_U1_59: R6.1, U1.59, U3.1
NET_U1_60: R12.1, U1.60
NET_U1_62: U13.3, U13.4
NET_U2_3: R11.1, U2.3
NET_U5_1: R15.1, U5.1
NET_U5_2: R16.1, U5.2
NET_U5_3: R17.1, U5.3
NET_U10_3: R19.1, U10.3
NET_U10_5: R18.1, U10.5
NET_U10_7: R20.2, R21.1, U10.7
NET_U11_1: C18.1, U11.1
NET_U11_6: R23.2, R24.1, U11.6
NET_U11_8: R22.1, U11.8
NET_U12_1: R26.1, R27.1, U12.1
NET_U12_3: R28.2, R29.1, U12.3
NET_U12_4: R25.1, U12.4, U15.2
NET_U13_1: R2.1, U13.1, U13.2
PROC_GPIO_TO_U1_USB_FAULT: R13.1, U1.4, U2.6
PROC_GPIO_TO_U1_VBUS_EN: R14.1, U1.2, U2.4
PROC_USB_OTG_FS_DM: U1.44, U6.2, U7.3
PROC_USB_OTG_FS_DP: U1.45, U6.3, U7.2
PROC_USB_OTG_FS_ID: U1.43, U6.4
PROC_USB_OTG_FS_VBUS: U1.42, U2.1, U6.1, U7.4
VCC_S1_8V4: C16.1, C19.1, C22.1, C23.1, J1.1, R19.2, R22.2, U10.8, U11.4
VCC_TIER1_3V3: C1.1, C2.1, C3.1, C4.1, C5.1, C6.1, C7.1, C11.1, C12.1, C13.1, C14.1, C15.1, C17.1, C21.1, C24.1, F1.2, R4.2, R5.2, R6.2, R7.2, R8.2, R9.2, R10.2, R13.2, R15.2, R16.2, R17.2, R18.2, R20.1, R25.2, R26.2, R28.1, U1.1, U1.19, U1.32, U1.48, U1.64, U3.5, U4.8, U5.8, U8.4, U9.4, U10.1, U12.6, U15.5
VCC_TIER1_5V0: C20.1, R23.1, U2.5, U11.5

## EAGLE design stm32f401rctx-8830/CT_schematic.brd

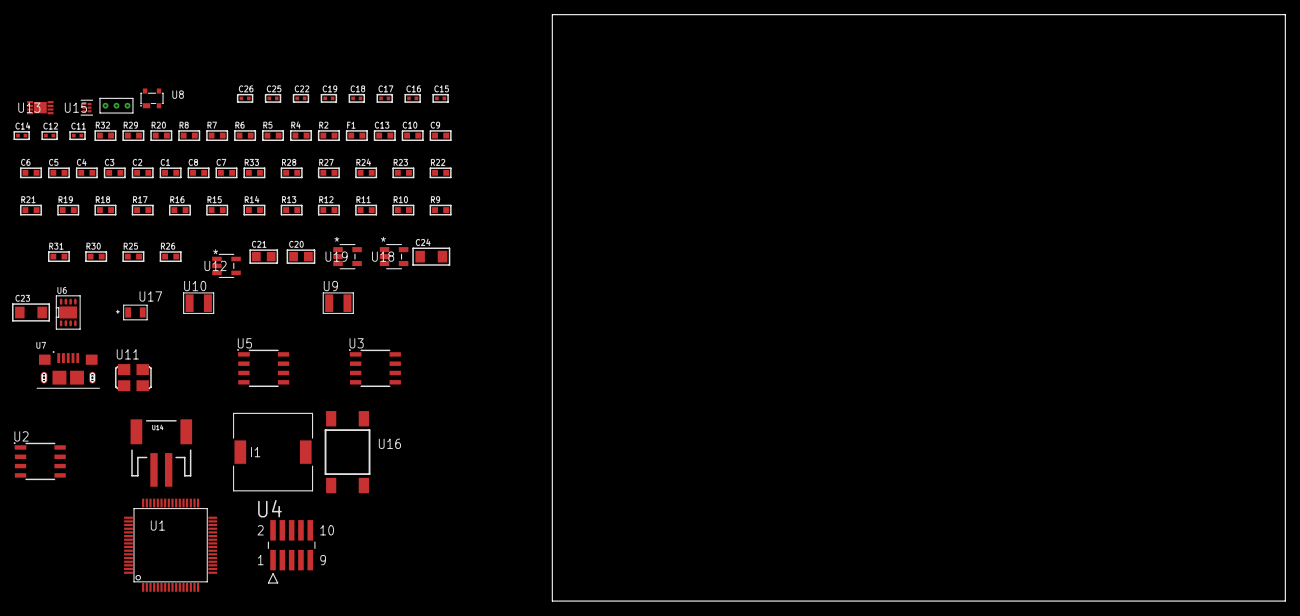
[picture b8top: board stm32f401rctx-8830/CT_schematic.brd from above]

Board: 2 copper layers, 169.6 x 80.0 mm, 79 parts (0 on the bottom side), 53 nets, no tracks yet.

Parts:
C1, C10, C13: 1e-06; C0603
C2, C3, C4, C5, C6: 1e-07; C0603
C7: 4.7e-06; C0603
C8: 2.2e-06; C0603
C9: 1e-08; C0603
C11, C12: 1e-11; C0402
C14, C15, C17, C19, C25, C26: 1e-08; C0402
C16, C18, C22: 1e-07; C0402
C20, C21: 1e-05; C0805
C23, C24: 1e-05; C1206
F1: 240.0; L0603
I1: 5.2e-06; DR1040
R2: 1000.0; R0603
R4: 4700.0; R0603
R5, R6, R7, R8: 2200.0; R0603
R9, R10, R11, R12, R13, R14, R15, R16, R17, R18, R19, R21, R22, R23, R24, R27, R28, R33: 10000.0; R0603
R20: 5.0; R0603
R25: 220000.0; R0603
R26: 1000000.0; R0603
R29: 9100.0; R0603
R30: 680000.0; R0603
R31: 120000.0; R0603
R32: 2000.0; R0603
U1: stm32f401RCT6; LQFP64
U2: AT25256B-SSHL-T; SOIC-8
U3: AT25320B-SSHL-T; SOIC-8
U4: FTSH-105-01-L-DV-K; SAMTEC_FTSH-105-01-L-DV-K
U5: 24AA1025T-I/SN; SOIC-8
U6: PCF85063TP/1Z; SON-8
U7: 10118193-0001LF; FCI_10118193-0001LF
U8: prtr5v0u2ax; SOT143B
U9, U10: ABS07-32.768KHZ-7-T
U11: ASFL1-25MHZ-NCS; ASFL1
U12: ltc3406es5; TSOT-23-5
U13: MCP73831T-2ACI/MC; DFN8_2X3MC
U14: S2B-PH-SM4-TB(LF)(SN); JST-2-SMD
U15: TPS3895ADRYR; SON-6
U16: 4-1437565-2; SW_4-1437565-2
U17: Q65110A2395; LGM67K-G1J2-24-Z
U18, U19: nc7sz125m5x; NC7SZ125M5X
U20: Dummy; DUMMY_PACKAGE_176

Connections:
CLK_CRYSTAL_U1_3: C11.1, U1.3, U10.1
CLK_CRYSTAL_U1_4: C12.1, U1.4, U10.2
CLK_CRYSTAL_U6_1: U6.1, U9.1
CLK_CRYSTAL_U6_2: U6.2, U9.2
CLK_U1_5: U1.5, U11.3
GND: C1.2, C2.2, C3.2, C4.2, C5.2, C6.2, C7.2, C8.2, C9.2, C10.2, C11.2, C12.2, C13.2, C14.2, C15.2, C16.2, C17.2, C18.2, C19.2, C20.2, C21.1, C21.2, C22.2, C23.2, C24.2, C25.2, C26.2, R2.2, R9.2, R19.2, R20.2, R23.2, R25.2, R29.2, R31.2, R32.2, U1.12, U1.18, U1.31, U1.44, U1.47, U1.63, U2.4, U3.4, U4.3, U4.5, U5.4, U6.4, U6.PAD, U7.5, U7.6, U7.7, U7.8, U7.9, U8.1, U11.2, U12.2, U13.6, U13.9, U14.2, U15.2, U17.C, U18.2, U18.3, U19.1, U19.3, U20.1
INPUT_USBPOWER_5V: C13.1, C23.1, R33.2, U1.42, U7.1, U8.4, U13.1, U13.2
NET_U1_7: R4.1, U1.7, U19.4
NET_U1_13: C9.1, C10.1, F1.1, U1.13
NET_U1_30: C8.1, U1.30
NET_U1_40: R8.1, U1.40, U5.5
NET_U1_41: R7.1, U1.41, U5.6
NET_U1_58: R5.1, U1.58, U6.6
NET_U1_59: R6.1, U1.59, U6.5
NET_U1_60: R9.1, U1.60
NET_U1_62: U16.3, U16.4
NET_U2_3: R10.1, U2.3
NET_U2_7: R12.1, U2.7
NET_U3_3: R13.1, U3.3
NET_U3_7: R15.1, U3.7
NET_U4_9: R20.1, U4.9
NET_U5_1: R22.1, U5.1
NET_U5_2: R23.1, U5.2
NET_U5_3: R21.1, U5.3
NET_U6_3: R24.1, U6.3
NET_U12_3: I1.1, U12.3
NET_U12_5: R25.1, R26.1, U12.5
NET_U12_ATNET_3: I1.2, R26.2
NET_U13_5: R33.1, U13.5
NET_U13_8: R32.1, U13.8
NET_U15_1: R28.1, R29.1, U15.1
NET_U15_3: R30.2, R31.1, U15.3
NET_U15_4: R27.1, U15.4, U18.4, U19.2
NET_U16_1: R2.1, U16.1, U16.2
PROC_SPI1_MISO: U1.22, U2.2
PROC_SPI1_MOSI: U1.23, U2.5
PROC_SPI1_NSS: R11.1, U1.20, U2.1
PROC_SPI1_SCK: U1.21, U2.6
PROC_SPI2_MISO: U1.10, U3.2
PROC_SPI2_MOSI: U1.11, U3.5
PROC_SPI2_NSS: R14.1, U1.33, U3.1
PROC_SPI2_SCK: U1.29, U3.6
PROC_SYS_JTCK_SWCLK: R19.1, U1.49, U4.4
PROC_SYS_JTDI: R17.1, U1.50, U4.8
PROC_SYS_JTDO_SWO: U1.55, U4.6
PROC_SYS_JTMS_SWDIO: R18.1, U1.46, U4.2
PROC_TIM1_CH2N: U1.26, U20.2
PROC_TIM1_CH3: U1.43, U20.3
PROC_USB_OTG_FS_DM: U1.44, U7.2, U8.3
PROC_USB_OTG_FS_DP: U1.45, U7.3, U8.2
RST_OUT_U4_JTAG_RST_B: R16.1, U4.10, U18.1
VCC_S1_3V7: C20.1, C24.1, U12.4, U13.3, U13.4, U14.1
VCC_TIER1_3V3: C1.1, C2.1, C3.1, C4.1, C5.1, C6.1, C7.1, C14.1, C15.1, C16.1, C17.1, C18.1, C19.1, C21.2, C22.1, C25.1, C26.1, F1.2, I1.2, R4.2, R5.2, R6.2, R7.2, R8.2, R10.2, R11.2, R12.2, R13.2, R14.2, R15.2, R16.2, R17.2, R18.2, R21.2, R22.2, R24.2, R26.2, R27.2, R28.2, R30.1, U1.1, U1.19, U1.32, U1.48, U1.64, U2.8, U3.8, U4.1, U5.7, U5.8, U6.8, U11.4, U15.6, U18.5, U19.5
